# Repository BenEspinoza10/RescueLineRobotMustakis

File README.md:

# Club Robótica Linea Rescue Line
Este es el repositorio de la línea de robótica Rescue Line Aquí encontrás todo lo necesario para ejecutar las sesiones de manera exitosa.

## Sesiones
- Las presentaciones PPT por sesión se pueden encontrar en el siguiente link: [Presentaciones](https://docs.google.com/presentation/d/1HhJf0Knq2RezBDOXF99ei00qkOhWetyh1tN6ezIQvbw/edit?usp=drive_link)

## Archivos de construcción
En la carpeta archivos de construcción se pueden encontrar los modelos 3D, svg y el Gerber de Dynamis

En caso de ser necesario, dentro de la carpeta RescueLineRobot, se encuentra el proyecto original en KiCad. Este contienen los esquemáticos de los circuitos y el diseño de la pcb. 

## Errores y sugerencia

En caso de que se encuentren errores de contenido y/o cualquier otro problema relacionado a las sesiones, por favor añadirlo como una Issue al repositorio, de esta manera se queda registro de los cambios realizados historicamente para futuras referencias en un único lugar.

---
*Trabajo realizado por Benjamin Espinoza para el programa de Ciencia y Tecnología de la Fundación Mustakis, 2024*

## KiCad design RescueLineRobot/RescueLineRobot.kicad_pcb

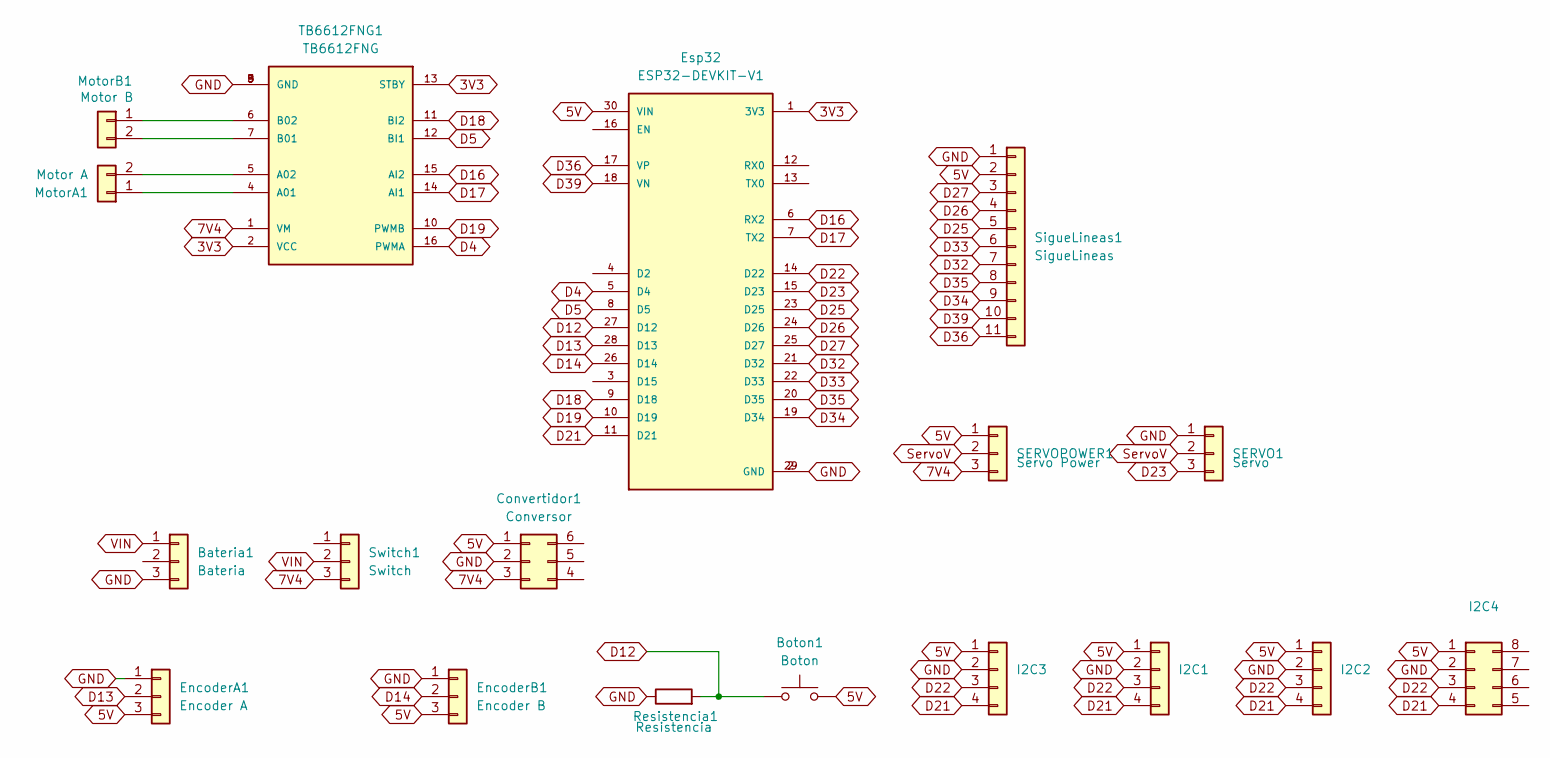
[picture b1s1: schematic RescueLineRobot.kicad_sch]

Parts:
Bateria1: Bateria; JST_XH_B3B-XH-A_1x03_P2.50mm_Vertical
Boton1: Boton; SW_PUSH-12mm
Convertidor1: Conversor; PinHeader_2x03_P2.54mm_Vertical
EncoderA1: Encoder A; JST_XA_B03B-XASK-1_1x03_P2.50mm_Vertical
EncoderB1: Encoder B; JST_XA_B03B-XASK-1_1x03_P2.50mm_Vertical
Esp32: ESP32-DEVKIT-V1; MODULE_ESP32_DEVKIT_V1; PARTREV N/A
I2C1, I2C2, I2C3, I2C4: JST_XH_B4B-XH-A_1x04_P2.50mm_Vertical
MotorA1: Motor A; JST_XH_B2B-XH-A_1x02_P2.50mm_Vertical
MotorB1: Motor B; JST_XH_B2B-XH-A_1x02_P2.50mm_Vertical
Resistencia1: Resistencia; R_Axial_DIN0617_L17.0mm_D6.0mm_P25.40mm_Horizontal
SERVO1: Servo; JST_XH_B3B-XH-A_1x03_P2.50mm_Vertical
SERVOPOWER1: Servo Power; PinHeader_1x03_P2.54mm_Vertical
SigueLineas1: SigueLineas; JST_XH_B11B-XH-A_1x11_P2.50mm_Vertical
Switch1: Switch; JST_XH_B3B-XH-A_1x03_P2.50mm_Vertical
TB6612FNG1: TB6612FNG; MODULE_ROB-14450; PARTREV 11-13-17

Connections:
3V3: Esp32.1 (3V3), TB6612FNG1.2 (VCC), TB6612FNG1.13 (STBY)
5V: Boton1.2, Convertidor1.1, EncoderA1.3, EncoderB1.3, Esp32.30 (VIN), I2C1.1, I2C2.1, I2C3.1, I2C4.1, SERVOPOWER1.1, SigueLineas1.2
7V4: Convertidor1.3, SERVOPOWER1.3, Switch1.3, TB6612FNG1.1 (VM)
D4: Esp32.5 (D4), TB6612FNG1.16 (PWMA)
D5: Esp32.8 (D5), TB6612FNG1.12 (BI1)
D12: Boton1.1, Esp32.27 (D12), Resistencia1.2
D13: EncoderA1.2, Esp32.28 (D13)
D14: EncoderB1.2, Esp32.26 (D14)
D16: Esp32.6 (RX2), TB6612FNG1.15 (AI2)
D17: Esp32.7 (TX2), TB6612FNG1.14 (AI1)
D18: Esp32.9 (D18), TB6612FNG1.11 (BI2)
D19: Esp32.10 (D19), TB6612FNG1.10 (PWMB)
D21: Esp32.11 (D21), I2C1.4, I2C2.4, I2C3.4, I2C4.4
D22: Esp32.14 (D22), I2C1.3, I2C2.3, I2C3.3, I2C4.3
D23: Esp32.15 (D23), SERVO1.3
D25: Esp32.23 (D25), SigueLineas1.5
D26: Esp32.24 (D26), SigueLineas1.4
D27: Esp32.25 (D27), SigueLineas1.3
D32: Esp32.21 (D32), SigueLineas1.7
D33: Esp32.22 (D33), SigueLineas1.6
D34: Esp32.19 (D34), SigueLineas1.9
D35: Esp32.20 (D35), SigueLineas1.8
D36: Esp32.17 (VP), SigueLineas1.11
D39: Esp32.18 (VN), SigueLineas1.10
GND: Bateria1.3, Convertidor1.2, EncoderA1.1, EncoderB1.1, Esp32.2 (GND), Esp32.29 (GND), I2C1.2, I2C2.2, I2C3.2, I2C4.2, Resistencia1.1, SERVO1.1, SigueLineas1.1, TB6612FNG1.3 (GND), TB6612FNG1.8 (GND), TB6612FNG1.9 (GND)
unnamed: MotorA1.1, TB6612FNG1.4 (A01)
unnamed: MotorA1.2, TB6612FNG1.5 (A02)
unnamed: MotorB1.1, TB6612FNG1.6 (B02)
unnamed: MotorB1.2, TB6612FNG1.7 (B01)
ServoV: SERVO1.2, SERVOPOWER1.2
VIN: Bateria1.1, Switch1.2

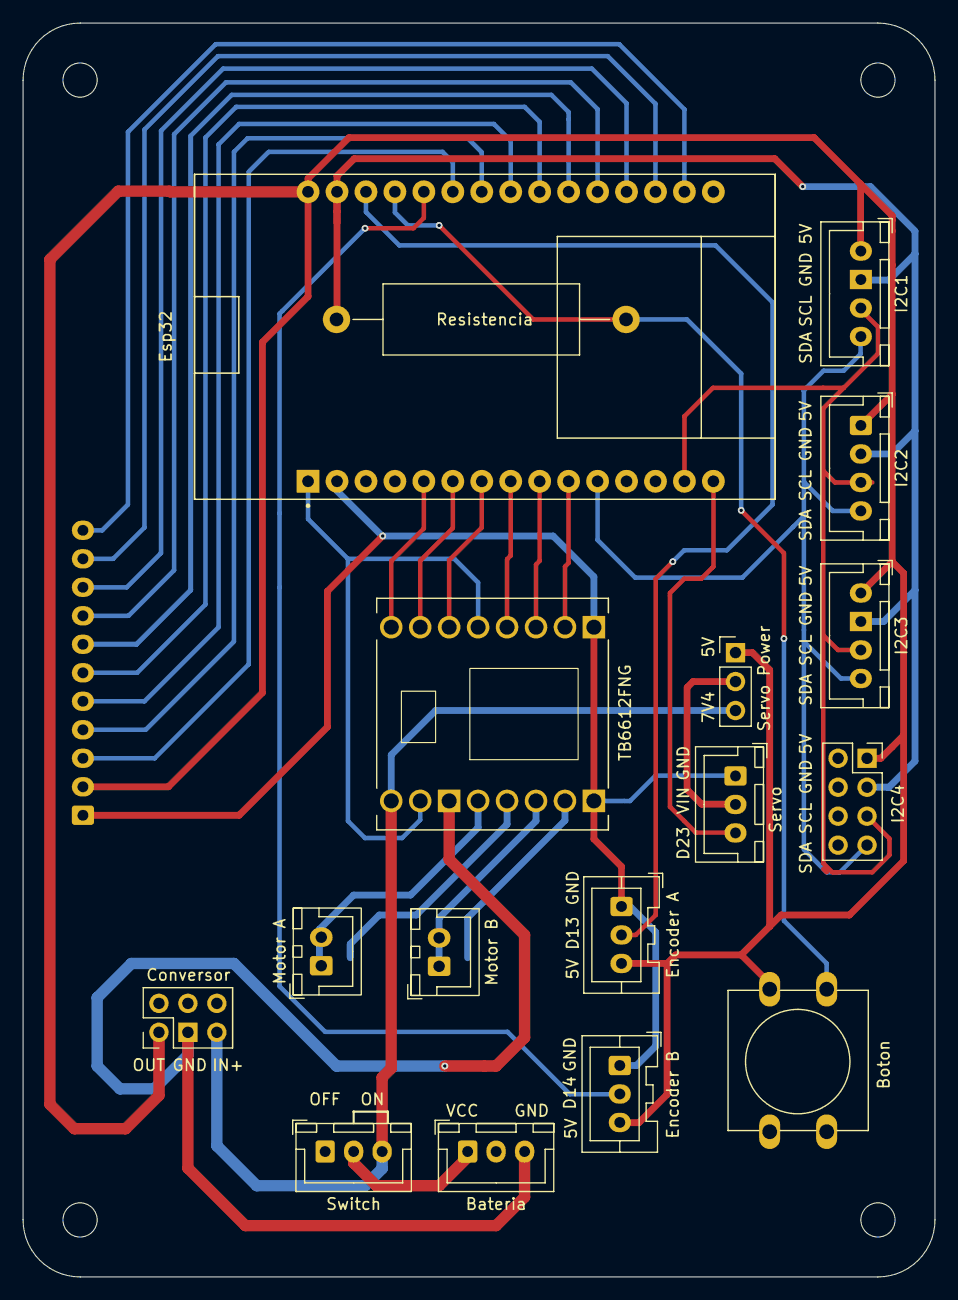
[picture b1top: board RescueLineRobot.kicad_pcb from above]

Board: 2 copper layers, 80.0 x 110.0 mm, 18 parts (1 on the bottom side), 31 nets.

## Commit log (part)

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2024-03-12 Sensor y motores
    Se ajustó cableado de puente h y sensores para que quede mas simple la pcb, el sensor funciona con un código sucio xd
2024-03-12 Motores funcionan :D
2024-03-13 Actualizacion de pcb
    Ahora la pcb está más limpia y con serigrafía
    Pendientes:
    -2 Sensores RGB
    -1 Botón pulsador
    -2 Encoders para los motores (aun no se si cuadraticos o no)
    -1 Puerto para servo (maybe con selector de voltaje)
2024-03-13 Boton y encoders
2024-03-14 Estamos Casi
    Están todas las rutas hechas, todos los puertos necesarios, sólo falta nombrar al robot y poner gráficas
2024-03-14 logo update
2024-03-18 Dynamis a nacido
    Estamos listos señores!!!
2024-04-06 Arreglo de dirección
2024-04-09 Create pruebaBoton.ino
    Se creo el archivo para probar el boton
2024-04-11 ni idea que sea esto xd
2024-05-17 main
2024-06-03 Ajustes
2024-07-29 Arreglo sensores
2024-07-29 preparacion final
2024-08-03 Motores fix
    Se arreglaron los headers de los motores para que sean consistentes en todos los robots
2024-08-03 Fix seguimiento línea
2024-08-03 Punto base
2024-09-13 No se que es esto xd
2025-02-27 Nueva versión
2025-03-25 Orden github
2025-03-25 Clase 2
2025-03-25 Name fix
2025-03-29 Update README.md
    Actualizacion link drive
2025-04-11 Update README.md
    Actualizacion link ppt
2025-04-21 Arreglos
2025-07-26 actualizaciones
2025-11-20 nueva rampa
2025-11-23 Encontré esto y mejor tener backup
2026-02-25 Dynamis V2
    - Sólo 4 i2c en la placa
    - Cambiar serigrafía de los motores hacia el lado superior
    - Agrandar puenteo para el voltaje del servo
    - Rotar conector de QTR hacia el lado más largo de la placa
2026-02-26 Arreglo regulador de voltaje
2026-02-27 Cambio giroscopio
    Se cambio el sistema de acople del giroscopio para que sea igual al del conversor de voltaje
2026-02-27 Creacion Gerber v2
2026-02-27 Fix GerberV2
2026-03-05 Last pcb changes
    Arreglo de puerto i2c para el giroscopio
2026-03-19 Fix manilla
    Se hizo mas profundo el hoyo para los insertos de metal
2026-03-19 Little fix manillas
2026-03-24 Codigos hasta clase 5
2026-03-27 Ilustraciones
2026-04-01 Nuevo codigo de pruebas generalizados solo para sensores
2026-04-02 Unificacion motor
2026-04-03 Update motores
    Ahora todo los motores funcionan bien
2026-05-20 Archivo fusion
    Se añadió el ultimo archivo de fusion360 del modelo del robot completo
2026-06-22 Ideas segundo semestre
    Hay que hacer sufrir a los NNJ
